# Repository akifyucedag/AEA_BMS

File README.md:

# AEA_BMS
iskenderun teknik üniversite  Alternatif araç topluluğu için hazırlamış olduğum 12s bms kartı

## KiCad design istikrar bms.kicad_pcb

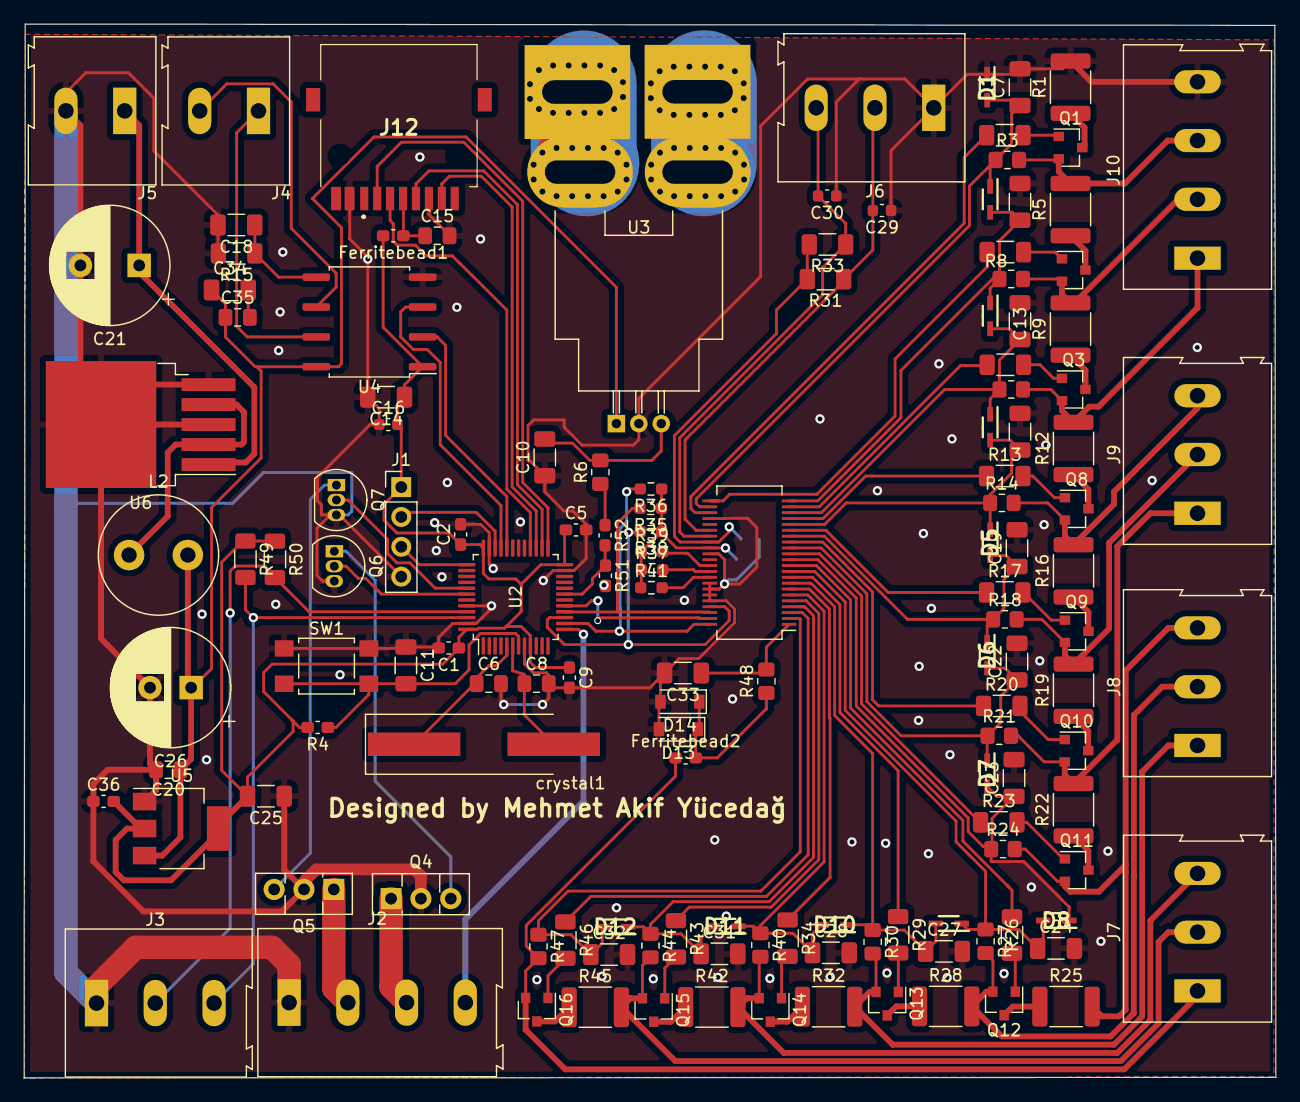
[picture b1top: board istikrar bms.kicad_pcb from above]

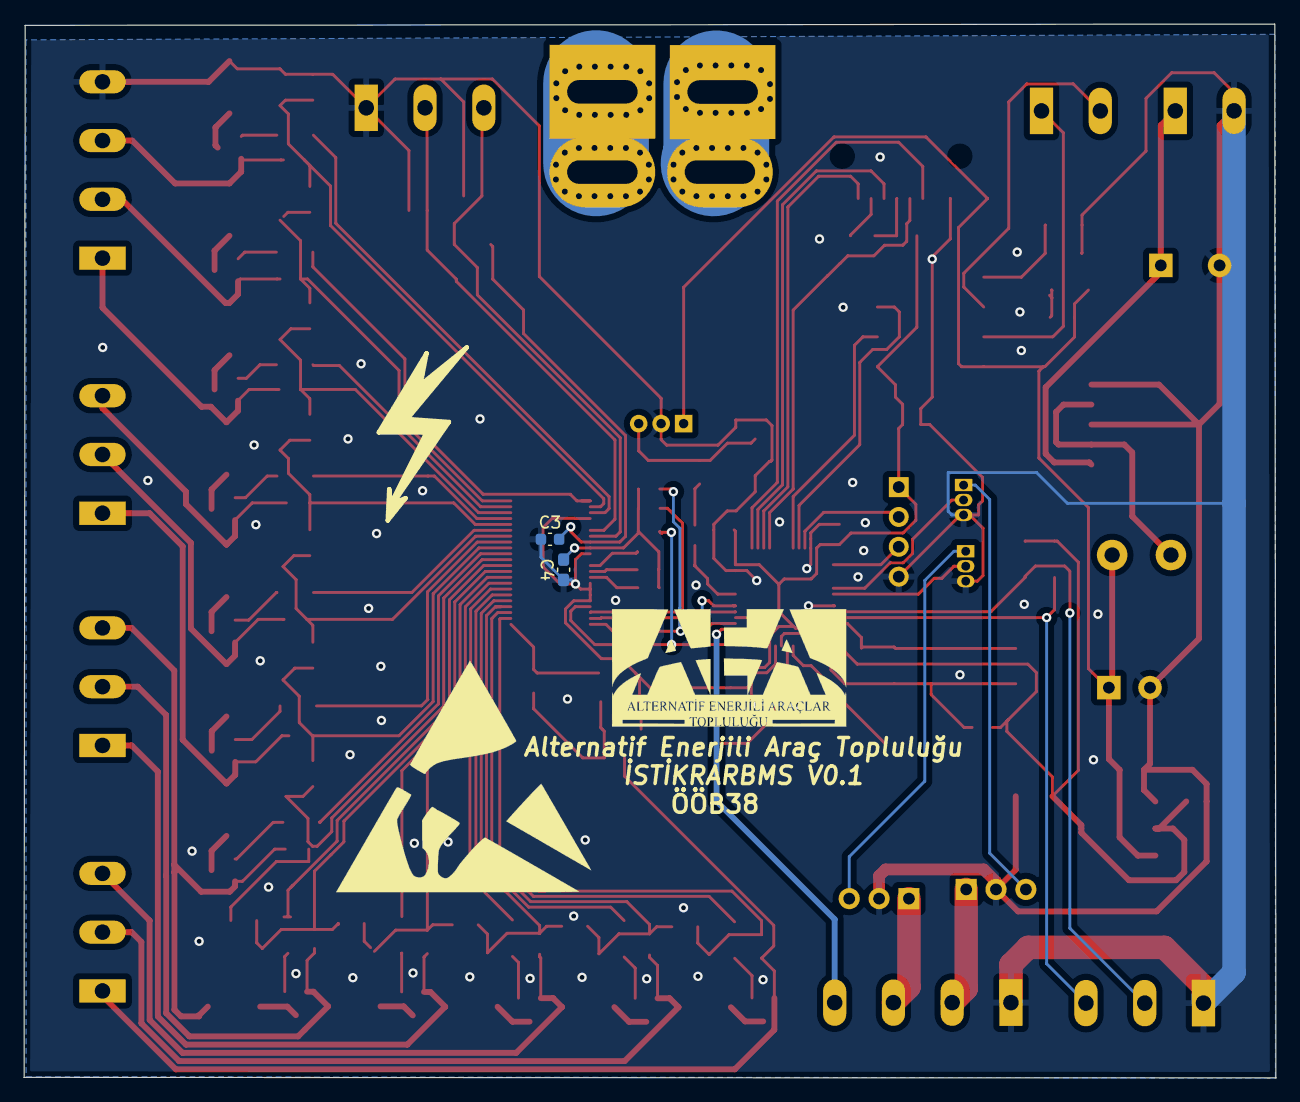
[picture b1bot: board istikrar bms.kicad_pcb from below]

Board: 2 copper layers, 106.5 x 89.7 mm, 141 parts (3 on the bottom side), 107 nets.

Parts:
 : Symbol_HighVoltage_Type1_CopperTop_Big
C1, C2, C5, C9: 100nf; C_0603_1608Metric_Pad1.08x0.95mm_HandSolder
C3: 1uf63v; C_0603_1608Metric
C4: 1uf63v; C_0603_1608Metric_Pad1.08x0.95mm_HandSolder
C6, C8: 18pf; C_0805_2012Metric_Pad1.18x1.45mm_HandSolder
C7, C12, C13, C17, C19, C22, C23, C24, C27, C28, C32: 100nf100v; C_1206_3216Metric_Pad1.33x1.80mm_HandSolder
C10, C14, C25: 100nf; C_1206_3216Metric_Pad1.33x1.80mm_HandSolder
C11, C34: 100nf 25v; C_1206_3216Metric_Pad1.33x1.80mm_HandSolder
C15, C20, C35: 10uf10V; C_0805_2012Metric_Pad1.18x1.45mm_HandSolder
C16, C29, C30: 1uf; C_0603_1608Metric
C18: 10nf100v; C_1206_3216Metric_Pad1.33x1.80mm_HandSolder
C21: 100uf; CP_Radial_D10.0mm_P5.00mm
C26: 330uf; CP_Radial_D10.0mm_P3.50mm
C31: 100nf1000v; C_1206_3216Metric_Pad1.33x1.80mm_HandSolder
C33: 100nf 100v; C_1206_3216Metric_Pad1.33x1.80mm_HandSolder
C36: 22uf; C_0603_1608Metric_Pad1.08x0.95mm_HandSolder
D1, D2, D3, D4, D5, D6, D7, D8, D9, D10, D11, D12: PDZ7.5B; SOD2512X110N
D13: MMSZ68V-HT; D_SOD-123
D14: 1N4148W-HT; D_SOD-123
Ferritebead1, Ferritebead2: BLM18PG330SN1D; C_0603_1608Metric_Pad1.08x0.95mm_HandSolder
J1: debug; PinHeader_1x04_P2.54mm_Vertical
J2: fan kontrol; TerminalBlock_Altech_AK300-4_P5.00mm
J3, J6, J7, J8, J9: Screw_Terminal_01x03; TerminalBlock_Altech_AK300-3_P5.00mm
J4: can port; TerminalBlock_Altech_AK300-2_P5.00mm
J5: 30V vin; TerminalBlock_Altech_AK300-2_P5.00mm
J10: Screw_Terminal_01x04; TerminalBlock_Altech_AK300-4_P5.00mm
J12: 112I-TDAR-R; 112ITDARR
L2: 100uh; L_Radial_D10.0mm_P5.00mm_Fastron_07M
Q1, Q2, Q3, Q8, Q9, Q10, Q11, Q12, Q13, Q14, Q15, Q16: PJA3417; SOT-23
Q4, Q5: BD140; TO-126-3_Vertical
Q6, Q7: BC547; TO-92_Inline
R1, R5, R9, R12, R16, R19, R22, R25, R28, R32, R42, R45: 33R; R_1812_4532Metric_Pad1.30x3.40mm_HandSolder
R2, R7, R10, R13, R17, R20, R23, R26, R29, R34, R43, R46, R49, R50: 3.3k; R_1206_3216Metric_Pad1.30x1.75mm_HandSolder
R3, R6, R8, R11, R14, R18, R21, R24, R27, R30, R40, R44, R47, R48: 100R; R_0805_2012Metric_Pad1.20x1.40mm_HandSolder
R4, R51, R52: 10k; C_0603_1608Metric_Pad1.08x0.95mm_HandSolder
R15: 4.7M; R_1206_3216Metric_Pad1.30x1.75mm_HandSolder
R31, R33: 100k; R_1206_3216Metric_Pad1.30x1.75mm_HandSolder
R35, R36, R37, R38, R39, R41: 1M; R_0603_1608Metric_Pad0.98x0.95mm_HandSolder
SW1: SW_Push; SW_SPST_TL3305C
U1: LTC6803-2; SSOP-44_5.3x12.8mm_P0.5mm
U2: STM32F303CCTx; LQFP-48_7x7mm_P0.5mm
U3: ACS770LCB; Allegro_CB_PFF
U4: ISO1050DUB; SOP-8_6.62x9.15mm_P2.54mm
U5: LM1117-3.3; SOT-223-3_TabPin2
U6: TL2575HV-33IKTTR; TO-263-5_TabPin6
crystal1: 8Mhz; Crystal_SMD_HC49-SD_HandSoldering

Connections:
+3V3: C1.1, C2.1, C5.1, C9.1, C14.1, C16.2, C25.2, C36.2, Ferritebead1.2, J1.1, R4.2, R49.1, R50.1, U2.9 (VDDA), U2.24 (VDD), U2.36 (VDD), U2.48 (VDD), U4.1 (VCC1), U5.2 (VO)
+5V: C20.1, C26.1, C34.1, C35.1, L2.2, U3.1 (VCC), U4.8 (VCC2), U5.3 (VI)
/+30V: C21.1, J5.1, U6.1 (VIN)
/C1: C7.1, D1.2 (K), D2.1 (A), R3.1, U1.24 (C1)
/C1+: J10.3, Q1.2 (S), R3.2, R5.2
/C2: D3.1 (A), R8.1, U1.22 (C2)
/C2+: J10.2, Q2.2 (S), R8.2, R9.2
/C3: C13.1, D3.2 (K), D4.1 (A), R11.1, U1.20 (C3)
/C3+: J10.1, Q3.2 (S), R11.2, R12.2
/C4: C17.1, D4.2 (K), D5.1 (A), R14.1, U1.18 (C4)
/C4+: J9.3, Q8.2 (S), R14.2, R16.2
/C5: C19.1, D5.2 (K), D6.1 (A), R18.1, U1.16 (C5)
/C5+: J9.2, Q9.2 (S), R18.2, R19.2
/C6: C22.1, D6.2 (K), D7.1 (A), R21.1, U1.14 (C6)
/C6+: J9.1, Q10.2 (S), R21.2, R22.2
/C7: C23.1, D7.2 (K), D8.1 (A), R24.1, U1.12 (C7)
/C7+: J8.3, Q11.2 (S), R24.2, R25.2
/C8: C24.1, D8.2 (K), D9.1 (A), R27.1, U1.10 (C8)
/C8+: J8.2, Q12.2 (S), R27.2, R28.2
/C9: D10.1 (A), R30.1, U1.8 (C9)
/C9+: J8.1, Q13.2 (S), R30.2, R32.2
/C10: C28.1, D10.2 (K), D11.1 (A), R40.1, U1.6 (C10)
/C10+: J7.3, Q14.2 (S), R40.2, R42.2
/C11: C31.1, D11.2 (K), D12.1 (A), R44.1, U1.4 (C11)
/C11+: J7.2, Q15.2 (S), R44.2, R45.2
/C12: C32.1, D12.2 (K), R47.1, U1.2 (C12)
/C12+: Ferritebead2.1, J7.1, Q16.2 (S), R47.2
/CLK: J12.5 (CLK), U2.26 (PB13)
/CMD: J12.3 (CMD), U2.28 (PB15)
/CSBI: R36.2, U1.44 (~CSBI), U2.14 (PA4)
/DAT0: J12.7 (DAT0), U2.27 (PB14)
/DAT3: J12.2 (CD/DAT3), U2.25 (PB12)
/GPIO1: R37.2, U1.35 (GPIO1)
/GPIO2: R41.2, U1.36 (GPIO2)
/PB5: Q7.2 (B), U2.41 (PB5)
/PB6: Q6.2 (B), U2.42 (PB6)
/RX: U2.32 (PA11), U4.2 (RXD)
/S1: R2.1, U1.25 (S1)
/S2: R7.1, U1.23 (S2)
/S3: R10.1, U1.21 (S3)
/S4: R13.1, U1.19 (S4)
/S5: R17.1, U1.17 (S5)
/S6: R20.1, U1.15 (S6)
/S7: R23.1, U1.13 (S7)
/S8: R26.1, U1.11 (S8)
/S9: R29.1, U1.9 (S9)
/S10: R34.1, U1.7 (S10)
/S11: R43.1, U1.5 (S11)
/S12: R46.1, U1.3 (S12)
/SCKI: R38.2, U1.41 (SCKI), U2.15 (PA5)
/SCL: J3.2, R50.2, U2.45 (PB8)
/SDA: J3.3, R49.2, U2.46 (PB9)
/SDI: R35.2, U1.42 (SDI), U2.16 (PA6)
/SDO: U1.43 (SDO), U2.17 (PA7)
/SWCLOCK: J1.3, U2.37 (PA14)
/SWIO: J1.2, U2.34 (PA13)
/TX: U2.33 (PA12), U4.3 (TXD)
/V+: C33.1, R48.2, U1.1 (V+)
/Vref: C3.2, R31.2, R33.2, U1.30 (Vref)
/WDBT: R39.2, U1.34 (~WDTB)
/currentadc: R51.1, R52.2, U2.19 (PB1)
/fan1: J2.3, Q4.1 (E)
/fan2: J2.2, Q5.1 (E)
/feedback1: L2.1, U6.2 (OUTPUT), U6.4 (FEEDBACK)
/flasor: J2.4, U2.13 (PA3)
/vreg: C4.2, R35.1, R36.1, R37.1, R38.1, R39.1, R41.1, U1.31 (Vreg)
/vtemp1: C29.2, J6.2, R31.1, U1.28 (Vtemp1)
/vtemp2: C30.2, J6.3, R33.1, U1.29 (Vtemp2)
GND: C1.2, C2.2, C3.1, C4.1, C5.2, C6.2, C7.2, C8.2, C9.2, C10.1, C11.1, C12.2, C13.2, C14.2, C15.2, C16.1, C17.2, C18.2, C19.2, C20.2, C21.2, C22.2, C23.2, C24.2, C25.1, C26.2, C27.2, C28.2, C29.1, C30.1, C31.2, C32.2, C33.2, C36.1, D1.1 (A), D13.2 (A), D14.2 (A), J1.4, J2.1, J3.1, J5.2, J6.1, J10.4, J12.6 (VSS), J12.9 (CD1/GND), Q4.2 (C), Q5.2 (C), Q6.3 (E), Q7.3 (E), R1.2, R15.2, R51.2, SW1.1, U1.26 (V-), U1.32 (TOS), U1.37 (A0), U1.38 (A1), U1.39 (A2), U1.40 (A3), U2.8 (VSSA), U2.23 (VSS), U2.35 (VSS), U2.44 (BOOT0), U2.47 (VSS), U3.2 (GND), U4.4 (GND1), U5.1 (GND), U6.3 (GND), U6.5 (~ON/OFF), U6.6 (GND)
unnamed: C6.1, U2.5 (PF0), crystal1.1
unnamed: C8.1, U2.6 (PF1), crystal1.2
unnamed: C10.2, R6.2, U3.3 (VIOUT)
unnamed: C11.2, R4.1, SW1.2, U2.7 (NRST)
unnamed: C12.1, D2.2 (K)
unnamed: C15.1, Ferritebead1.1, J12.4 (VDD)
unnamed: C18.1, C34.2, C35.2, R15.1, U4.5 (GND2)
unnamed: C27.1, D9.2 (K)
unnamed: D13.1 (K), D14.1 (K), Ferritebead2.2, R48.1
unnamed: J4.1, U4.7 (CANH)
unnamed: J4.2, U4.6 (CANL)
unnamed: Q1.1 (G), R2.2
unnamed: Q1.3 (D), R1.1
unnamed: Q2.1 (G), R7.2
unnamed: Q2.3 (D), R5.1
unnamed: Q3.1 (G), R10.2
unnamed: Q3.3 (D), R9.1
unnamed: Q4.3 (B), Q6.1 (C)
unnamed: Q5.3 (B), Q7.1 (C)
unnamed: Q8.1 (G), R13.2
unnamed: Q8.3 (D), R12.1
unnamed: Q9.1 (G), R17.2
unnamed: Q9.3 (D), R16.1
unnamed: Q10.1 (G), R20.2
unnamed: Q10.3 (D), R19.1
unnamed: Q11.1 (G), R23.2
unnamed: Q11.3 (D), R22.1
unnamed: Q12.1 (G), R26.2
unnamed: Q12.3 (D), R25.1
unnamed: Q13.1 (G), R29.2
unnamed: Q13.3 (D), R28.1
unnamed: Q14.1 (G), R34.2
unnamed: Q14.3 (D), R32.1
unnamed: Q15.1 (G), R43.2
unnamed: Q15.3 (D), R42.1
unnamed: Q16.1 (G), R46.2
unnamed: Q16.3 (D), R45.1
unnamed: R6.1, R52.1
